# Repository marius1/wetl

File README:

WETL stands for Wifi Enabled Traffic Light. 

In the base it is an ESP-8266 with an http server on it, forked from sprite_tm's awesome work. See README.esp-httpd for more info on that.

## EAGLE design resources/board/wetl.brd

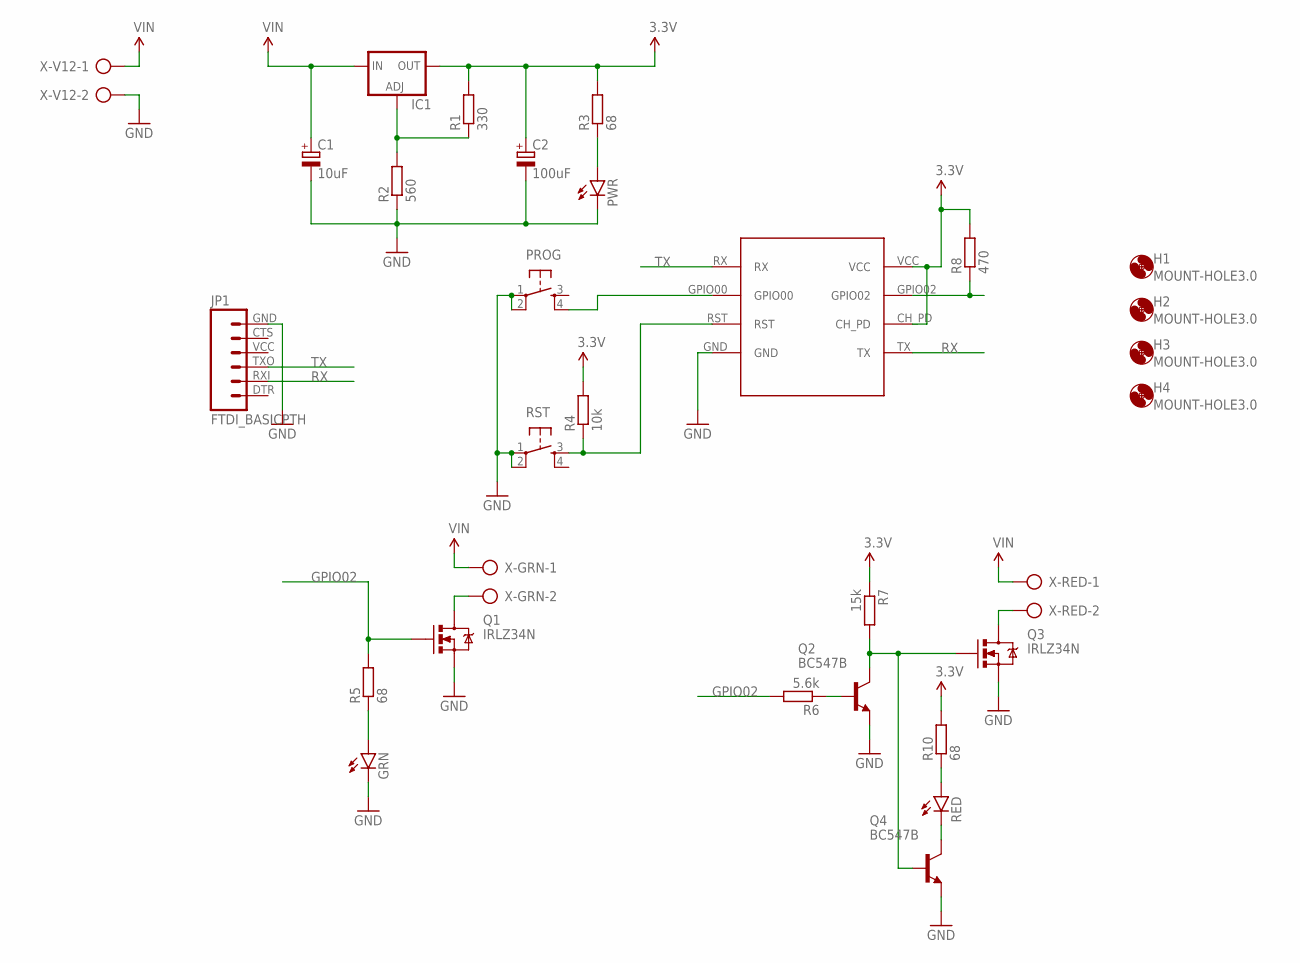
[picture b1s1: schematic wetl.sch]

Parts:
C1: 10uF; E2,5-6
C2: 100uF; E2,5-6
GRN: LED5MM
H1, H2, H3, H4: MOUNT-HOLE3.0; 3,0
IC1: LM317TS; 317TS
JP1: FTDI_BASICPTH; FTDI_BASIC
PROG: TAC_SWITCHPTH; TACTILE-PTH
PWR: LED5MM
Q1, Q3: IRLZ34N; TO220V
Q2, Q4: BC547B; TO92
R1: 330; 0204V
R2: 560; 0204V
R3, R5, R10: 68; 0204V
R4: 10k; 0204/7
R6: 5.6k; 0204V
R7: 15k; 0204V
R8: 470; 0204/7
RED: LED5MM
RST: TAC_SWITCHPTH; TACTILE-PTH
U$2: ESP8266; ESP-01
X-GRN: SMKDSP_1,5/2
X-RED: SMKDSP_1,5/2
X-V12: SMKDSP_1,5/2

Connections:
3.3V: C2.+, IC1.2 (OUT), R1.2, R3.2, R4.2, R7.1, R8.2, R10.2, U$2.CH_PD, U$2.VCC
GND: C1.-, C2.-, GRN.K (C), JP1.GND (6), PROG.1, PROG.2, PWR.K (C), Q1.3 (S), Q2.1 (E), Q3.3 (S), Q4.1 (E), R2.1, RST.1, RST.2, U$2.GND, X-V12.2
GPIO02: Q1.1 (G), R5.2, R6.2, R8.1, U$2.GPIO02
unnamed: GRN.A, R5.1
unnamed: IC1.1 (ADJ), R1.1, R2.2
unnamed: R10.1, RED.A
unnamed: Q3.2 (D), X-RED.2
unnamed: PWR.A, R3.1
unnamed: R4.1, RST.3, U$2.RST
unnamed: Q1.2 (D), X-GRN.2
unnamed: Q2.3 (C), Q3.1 (G), Q4.2 (B), R7.2
unnamed: Q2.2 (B), R6.1
unnamed: Q4.3 (C), RED.K (C)
unnamed: PROG.4, U$2.GPIO00
RX: JP1.RXI (2), U$2.TX
TX: JP1.TXO (3), U$2.RX
VIN: C1.+, IC1.3 (IN), X-GRN.1, X-RED.1, X-V12.1

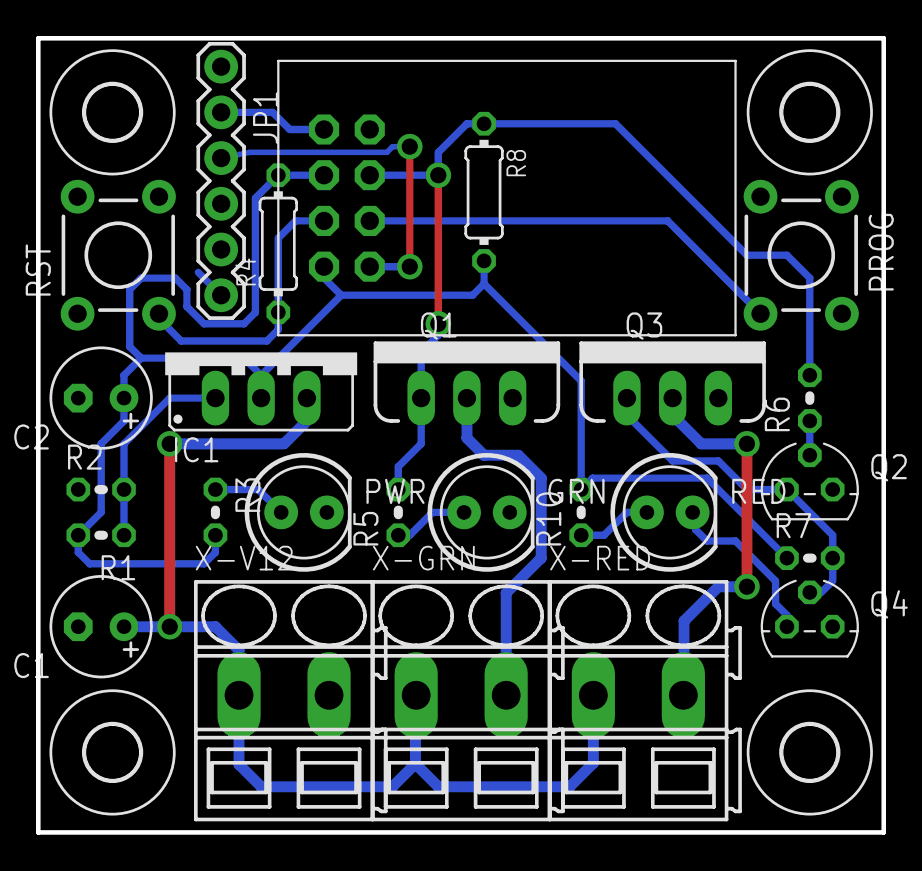
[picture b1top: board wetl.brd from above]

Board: 2 copper layers, 47.0 x 44.1 mm, 30 parts (0 on the bottom side), 17 nets.

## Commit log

2015-02-22 Added cgiGetLed
2015-02-22 First setup for template
2015-02-22 Removed old template
2015-02-22 photoshop files images
2015-02-22 Changed some stuff around, created custom mini jquery
2015-02-22 Added build 'script' for jquery custom
2015-02-24 Make bootstrap smaller
2015-02-24 Updated psd's
2015-02-25 Added method to connection data, changed cgiLed to know about this. Removed cgiGetLed. led.tpl now get's gpio pin state
2015-02-25 Bootstrap back
2015-04-01 New website test
2015-04-01 Moved images
2015-04-01 First design case
2015-04-13 Moved to Inkscape
2015-04-13 Move esp-httpd README
2015-04-13 New README file
2015-04-13 Deeper case, tabs are sized to 4,7mm panel
2015-04-13 Remove Illustrator files
2015-04-13 Added eagle board files
2015-04-15 Some changes for printing
2015-05-31 Stuff
2017-07-09 Remove old version
2017-07-09 Rewrite of the code
2020-03-02 Move photos in repo
2020-03-02 Now with correct uri

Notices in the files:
parts and their libraries:
SparkFun-Connectors: Licensing: Creative Commons ShareAlike 4.0 International - https://creativecommons.org/licenses/by-sa/4.0
